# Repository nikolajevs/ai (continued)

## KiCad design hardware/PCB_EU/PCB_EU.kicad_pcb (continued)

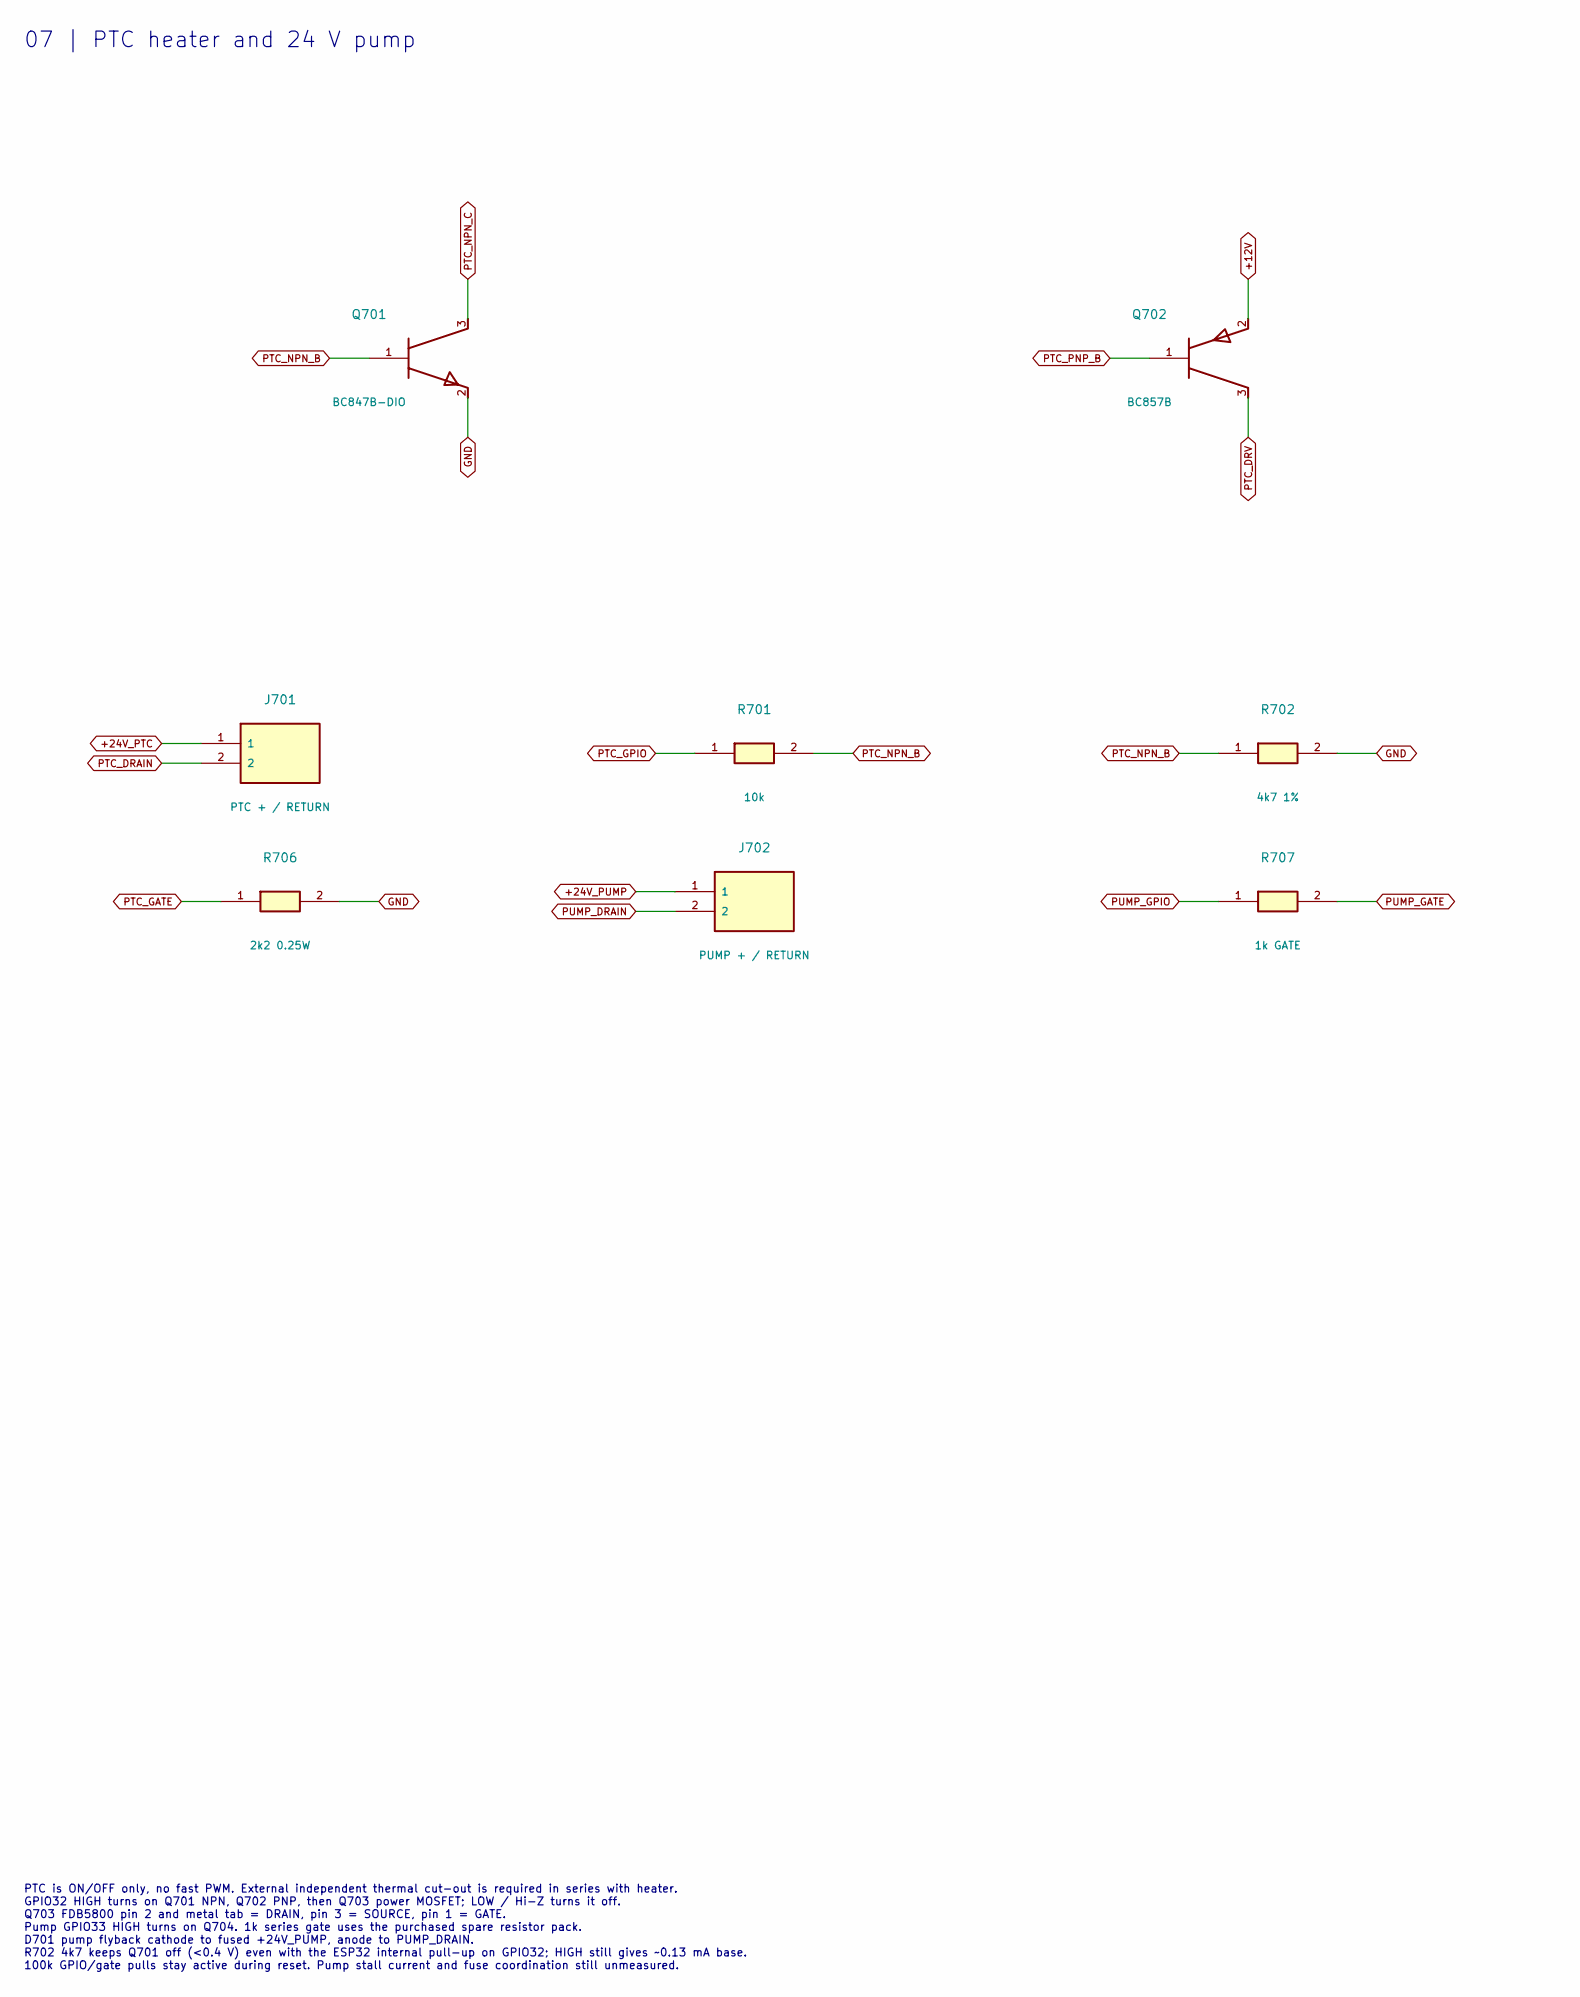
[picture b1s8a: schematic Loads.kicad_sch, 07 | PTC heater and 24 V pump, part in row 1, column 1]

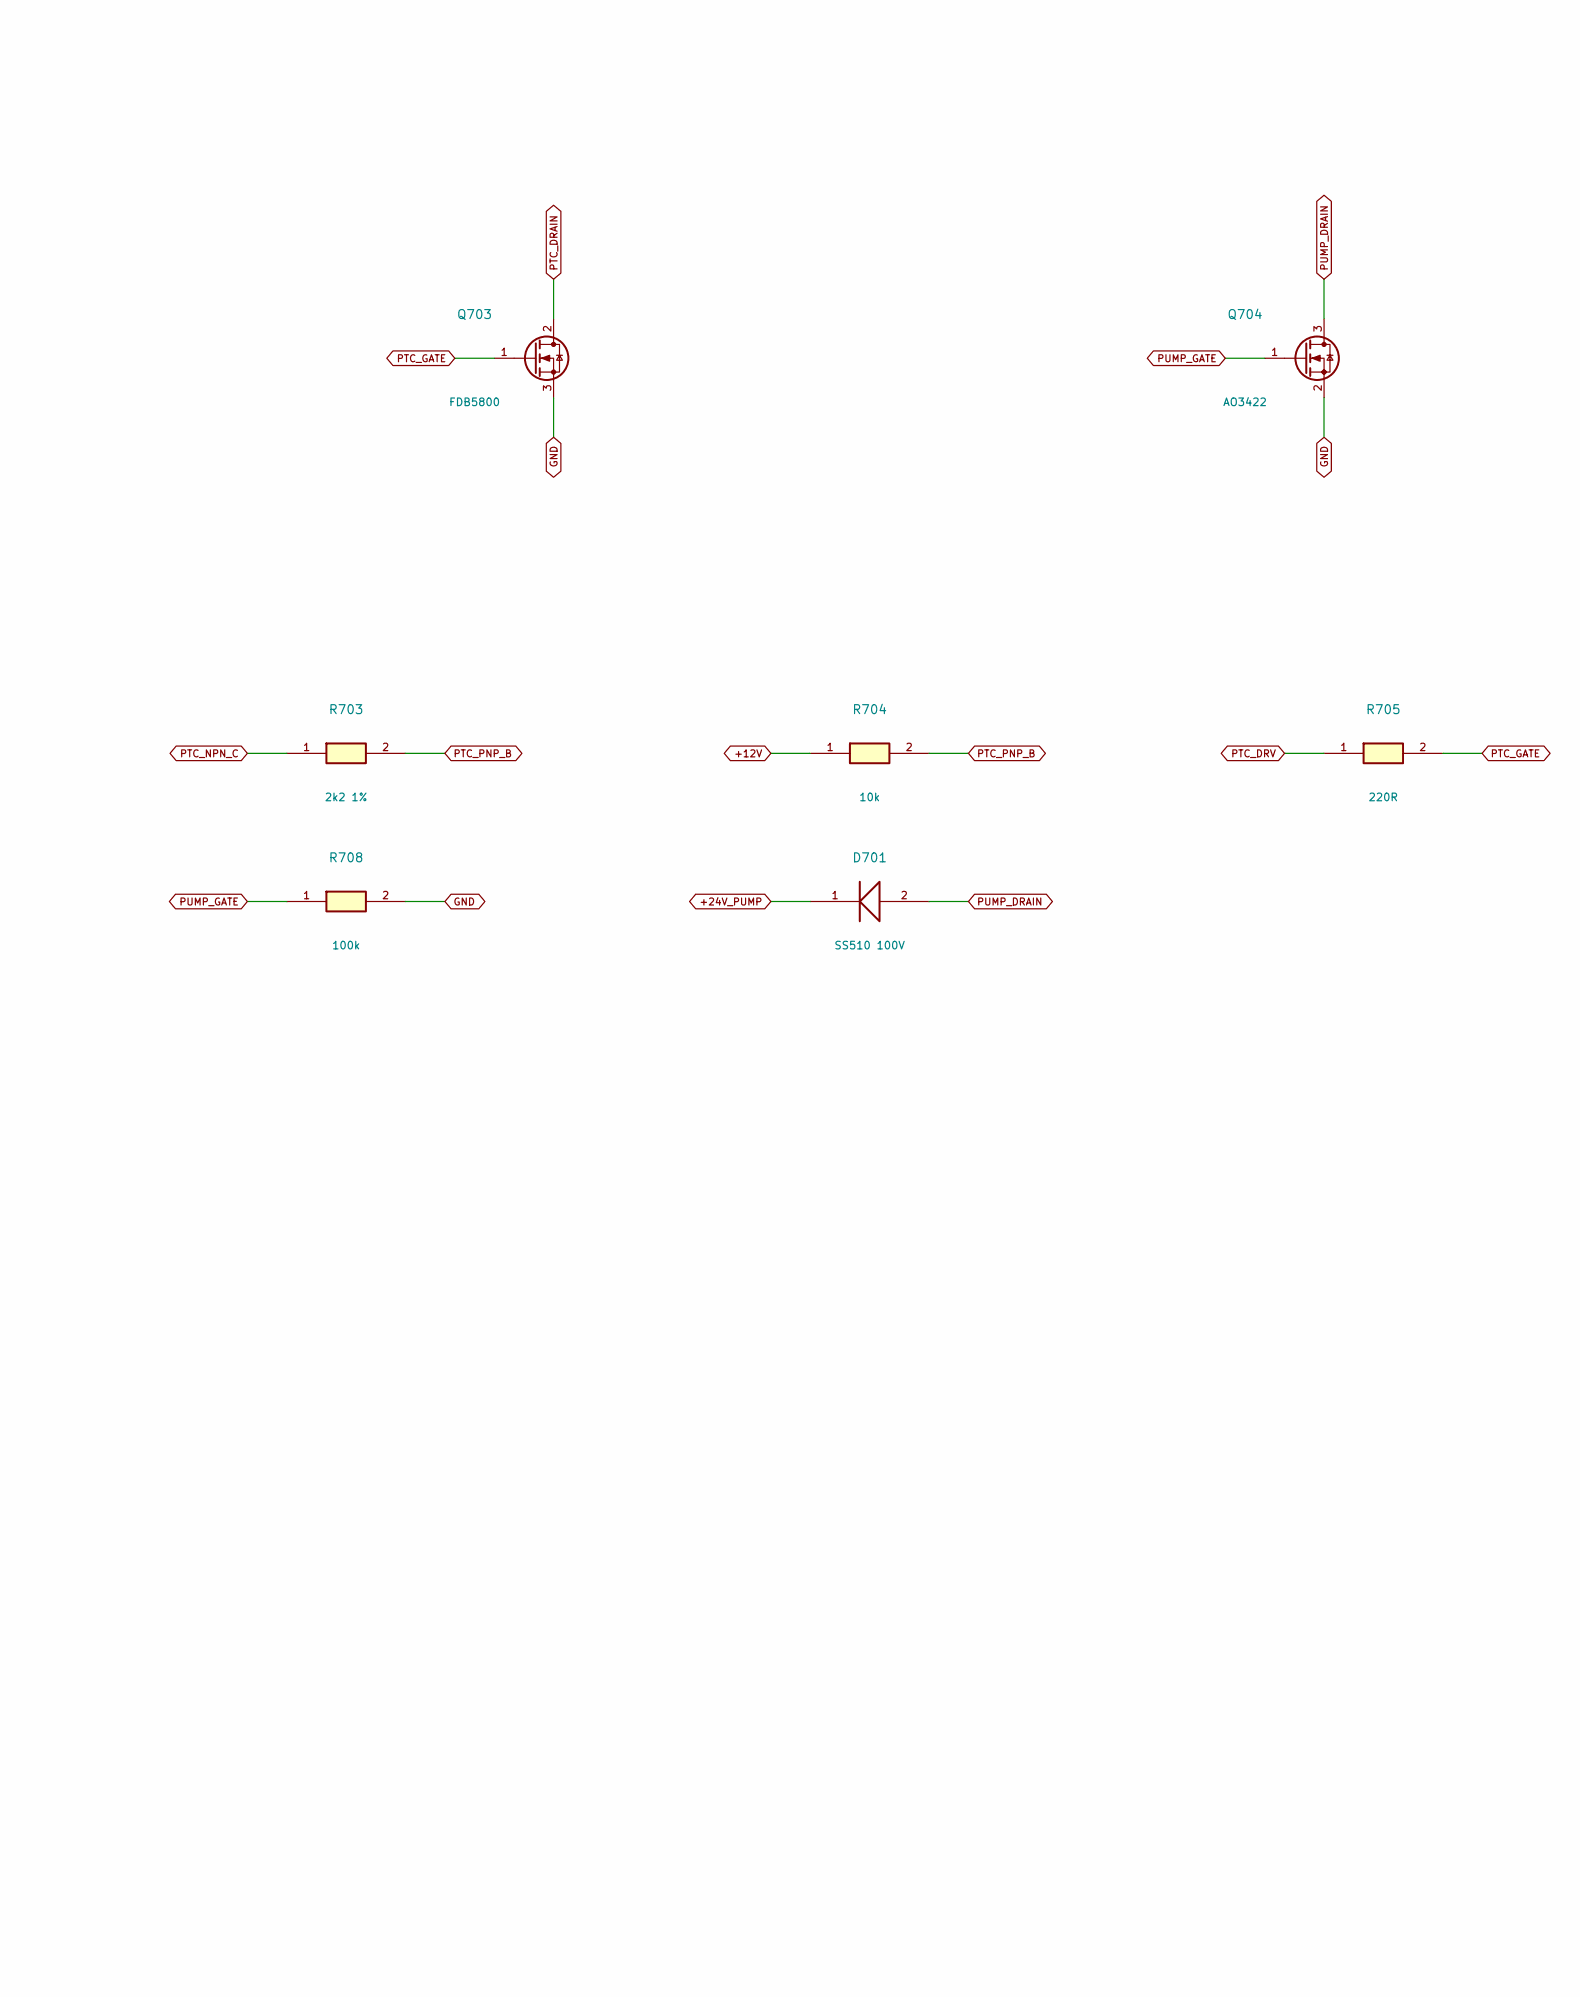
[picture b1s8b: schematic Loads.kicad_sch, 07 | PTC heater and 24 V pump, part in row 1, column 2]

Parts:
D701: SS510 100V; D_SMC; MPN SS510-YAN
J701: PTC + / RETURN; TerminalBlock_Degson_DG306-5.0_1x02; MPN DG306-5.0-2P12
J702: PUMP + / RETURN; TerminalBlock_Degson_DG306-5.0_1x02; MPN DG306-5.0-2P12
Q701: BC847B-DIO; SOT-23; MPN BC847B-DIO
Q702: BC857B; SOT-23; MPN BC857B
Q703: FDB5800; TO-263-2; MPN FDB5800
Q704: AO3422; SOT-23; MPN AO3422
R701, R704: 10k; R_0603_1608Metric; MPN SMD0603-10K
R702: 4k7 1%; R_1206_3216Metric; MPN SMD1206 4K7 1%
R703: 2k2 1%; R_1206_3216Metric; MPN SMD1206-2K2-1%
R705: 220R; R_1206_3216Metric; MPN SMD1206-220R-1%
R706: 2k2 0.25W; R_1206_3216Metric; MPN SMD1206-2K2-1%
R707: 1k GATE; R_0603_1608Metric; MPN SMD0603-1K
R708: 100k; R_0603_1608Metric; MPN SMD0603-100K

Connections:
+12V: Q702.2 (E), R704.1; also elsewhere on the board
+24V_PTC: J701.1; also elsewhere on the board
+24V_PUMP: D701.1 (K), J702.1; also elsewhere on the board
GND: Q701.2 (E), Q703.3 (S), Q704.2 (S), R702.2, R706.2, R708.2; also elsewhere on the board
PTC_DRAIN: J701.2, Q703.2 (D)
PTC_DRV: Q702.3 (C), R705.1
PTC_GATE: Q703.1 (G), R705.2, R706.1
PTC_GPIO: R701.1; also elsewhere on the board
PTC_NPN_B: Q701.1 (B), R701.2, R702.1
PTC_NPN_C: Q701.3 (C), R703.1
PTC_PNP_B: Q702.1 (B), R703.2, R704.2
PUMP_DRAIN: D701.2 (A), J702.2, Q704.3 (D)
PUMP_GATE: Q704.1 (G), R707.2, R708.1
PUMP_GPIO: R707.1; also elsewhere on the board

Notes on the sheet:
07 | PTC heater and 24 V pump
PTC is ON/OFF only, no fast PWM. External independent thermal cut-out is required in series with heater. GPIO32 HIGH turns on Q701 NPN, Q702 PNP, then Q703 power MOSFET; LOW / Hi-Z turns it off. Q703 FDB5800 pin 2 and metal tab = DRAIN, pin 3 = SOURCE, pin 1 = GATE. Pump GPIO33 HIGH turns on Q704. 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

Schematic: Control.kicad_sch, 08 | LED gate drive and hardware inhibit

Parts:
C803: 100n; C_0805_2012Metric; MPN CL21B104KBCNNNC
D801: BAT54-DIO; SOT-23; MPN BAT54-DIO
R803, R807: 4R7 1W; R_2512_6332Metric; MPN SMD2512-4R7
R804, R808: 100k; R_0603_1608Metric; MPN SMD0603-100K
R809: 56k 1%; R_1206_3216Metric; MPN SMD1206 56K 1%
R810, R811, R816: 5k6 1%; R_1206_3216Metric; MPN SMD1206 5K6 1%
R812: 1M 1%; R_1206_3216Metric; MPN SMD1206-1M-1%
R813, R814: 10k 1%; R_1206_3216Metric; MPN SMD1206-10K-1%
R815: 10k; R_0603_1608Metric; MPN SMD0603-10K
R817: 10k SHARED; R_0603_1608Metric; MPN SMD0603-10K
TP03: LED_NDIM; TestPoint_Pad_D1.0mm
TP04: BLOCK_OC; TestPoint_Pad_D1.0mm
TP05: UVLO_SENSE; TestPoint_Pad_D1.0mm
TP06: UVLO_REF; TestPoint_Pad_D1.0mm
U802: LM2903D-ST; SOIC-8_3.9x4.9mm_P1.27mm; MPN LM2903D-ST

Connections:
+3V3: R813.1, R815.1; also elsewhere on the board
+12V: C803.1, U802.8 (VCC); also elsewhere on the board
+24V_FUSED: R809.1; also elsewhere on the board
BLOCK_OC: D801.3 (K), R812.1, R815.2, TP04.1, U802.1 (OUT1); also elsewhere on the board
GND: C803.2, R804.2, R808.2, R811.2, R814.2, R817.2, U802.4 (GND), U802.5 (IN2+); also elsewhere on the board
LED1_GATE: R803.2, R804.1; also elsewhere on the board
LED1_GATE_RAW: R803.1; also elsewhere on the board
LED2_GATE: R807.2, R808.1; also elsewhere on the board
LED2_GATE_RAW: R807.1; also elsewhere on the board
LED_NDIM: D801.1 (A), R816.2, R817.1, TP03.1; also elsewhere on the board
LED_PWM_GPIO: R816.1; also elsewhere on the board
UVLO_REF: R813.2, R814.1, TP06.1, U802.2 (IN1-), U802.6 (IN2-)
UVLO_SENSE: R810.2, R811.1, R812.2, TP05.1, U802.3 (IN1+)
UVLO_TOP_MID: R809.2, R810.1

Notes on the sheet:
08 | LED gate drive and hardware inhibit
BLOCK_OC is wired OR: L7987 PGOOD + LM2903 output, pulled up only to +3V3. BAT54 anode -> nDIM; cathode -> BLOCK_OC. Do not reverse this diode. One shared 10k pull-down on nDIM defeats BOTH internal LM3429 hysteresis sources after MCU reset. Do NOT add a 100n capacitor to nDIM. GPIO25 HIGH is enabl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

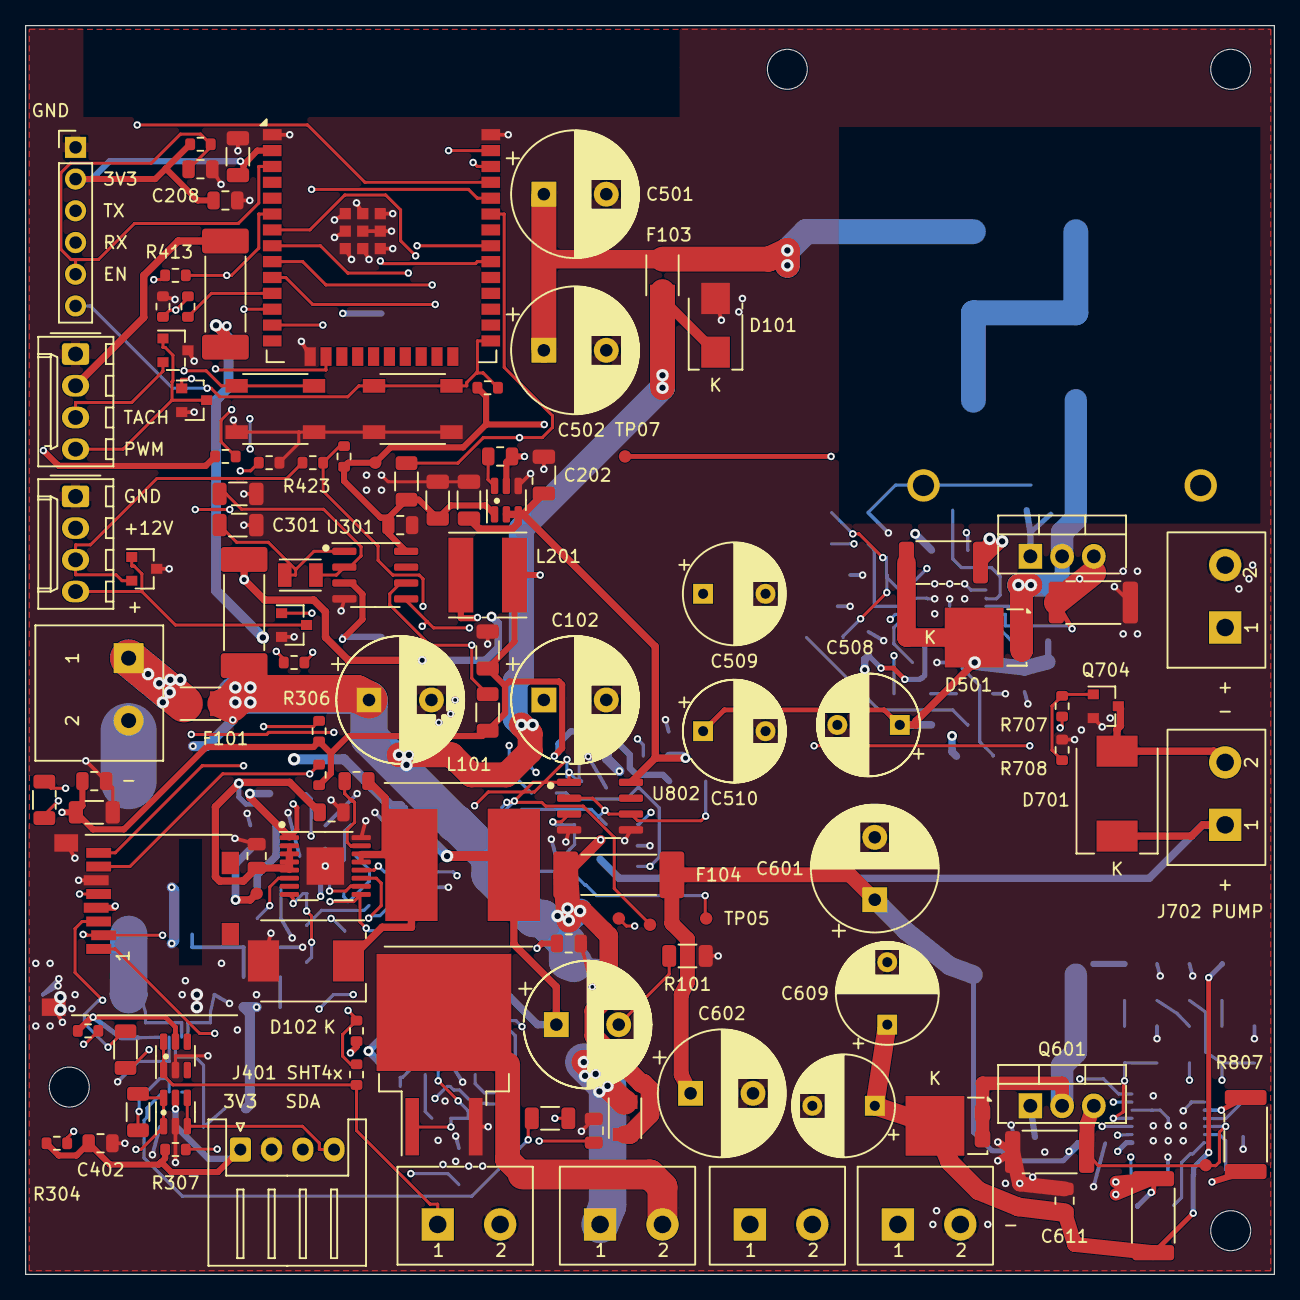
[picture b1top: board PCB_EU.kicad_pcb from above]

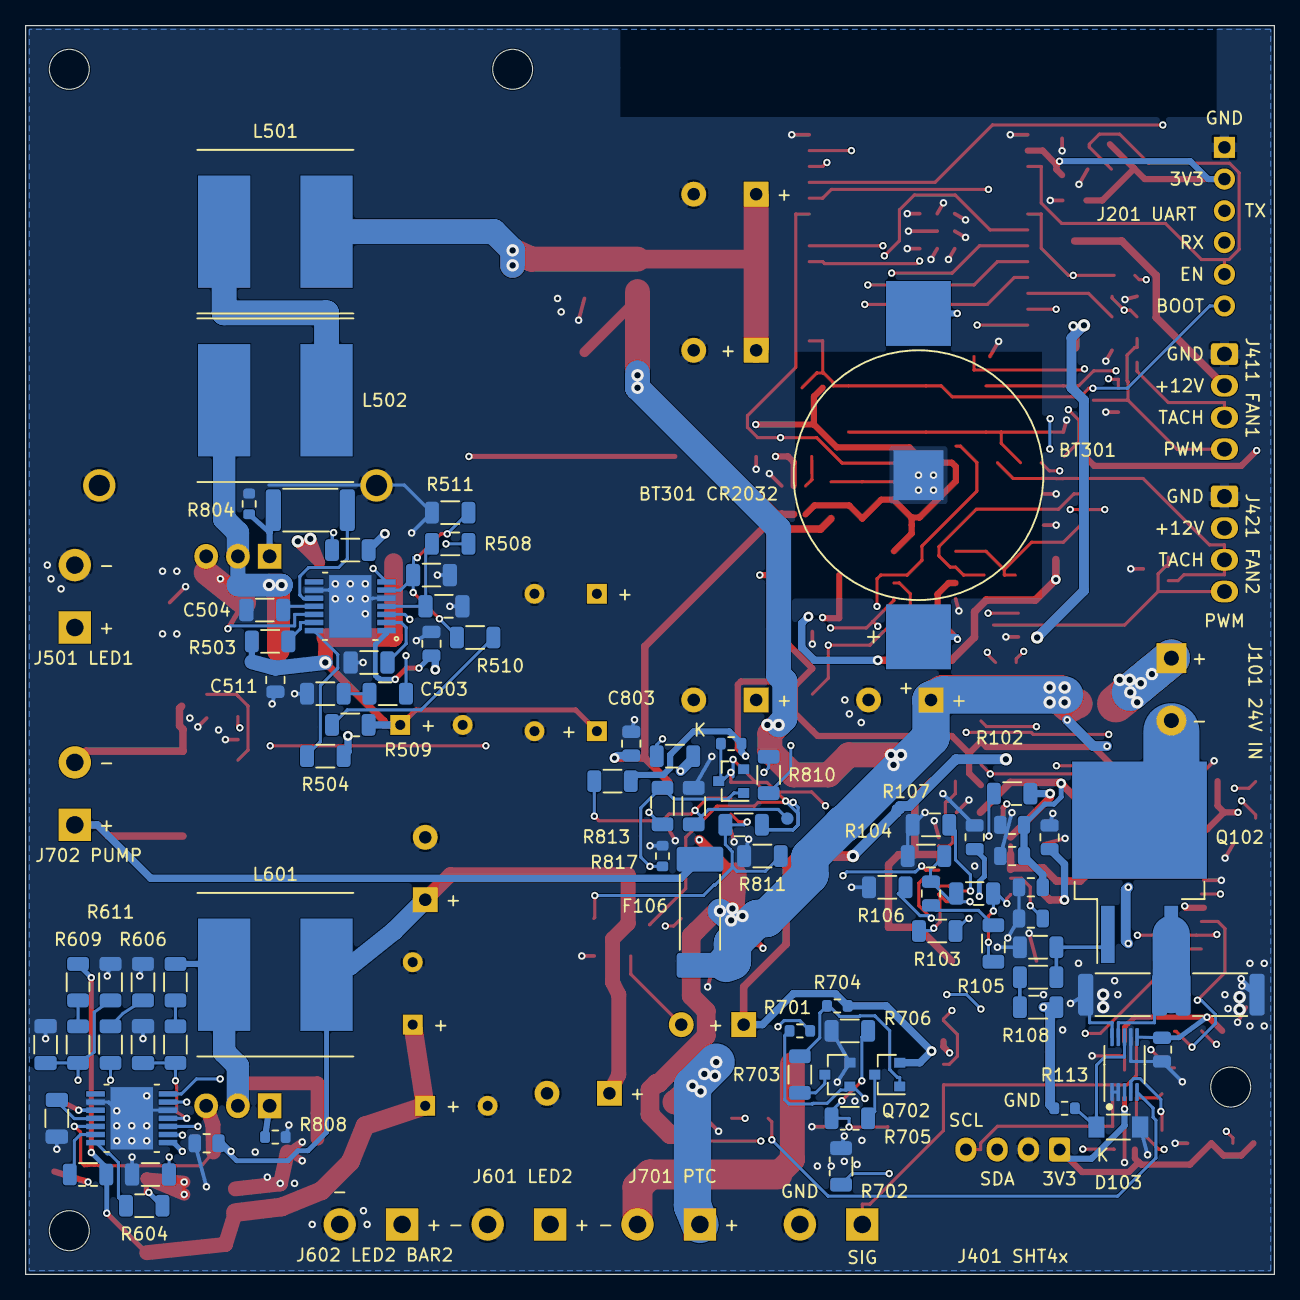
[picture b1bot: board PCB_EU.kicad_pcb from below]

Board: 4 copper layers, 100.0 x 100.0 mm, 201 parts (83 on the bottom side), 108 nets.

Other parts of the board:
H1, H2, H3, H4: M3 NPTH 3.2 / proposed
HS1: RAD-DY-GF/3 pins 2x d1.4 / GND

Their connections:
GND: HS1.1, HS1.2; also elsewhere on the board
